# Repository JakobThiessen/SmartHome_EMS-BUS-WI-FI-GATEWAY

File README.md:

# SmartHome_EMS-BUS-WI-FI-GATEWAY
ESP32-EMS WiFi gateway for read and control EMS and Heatronic compatible devices such as boilers, thermostats, solar modules and heat pumps.

# Software Project

https://github.com/emsesp/EMS-ESP32

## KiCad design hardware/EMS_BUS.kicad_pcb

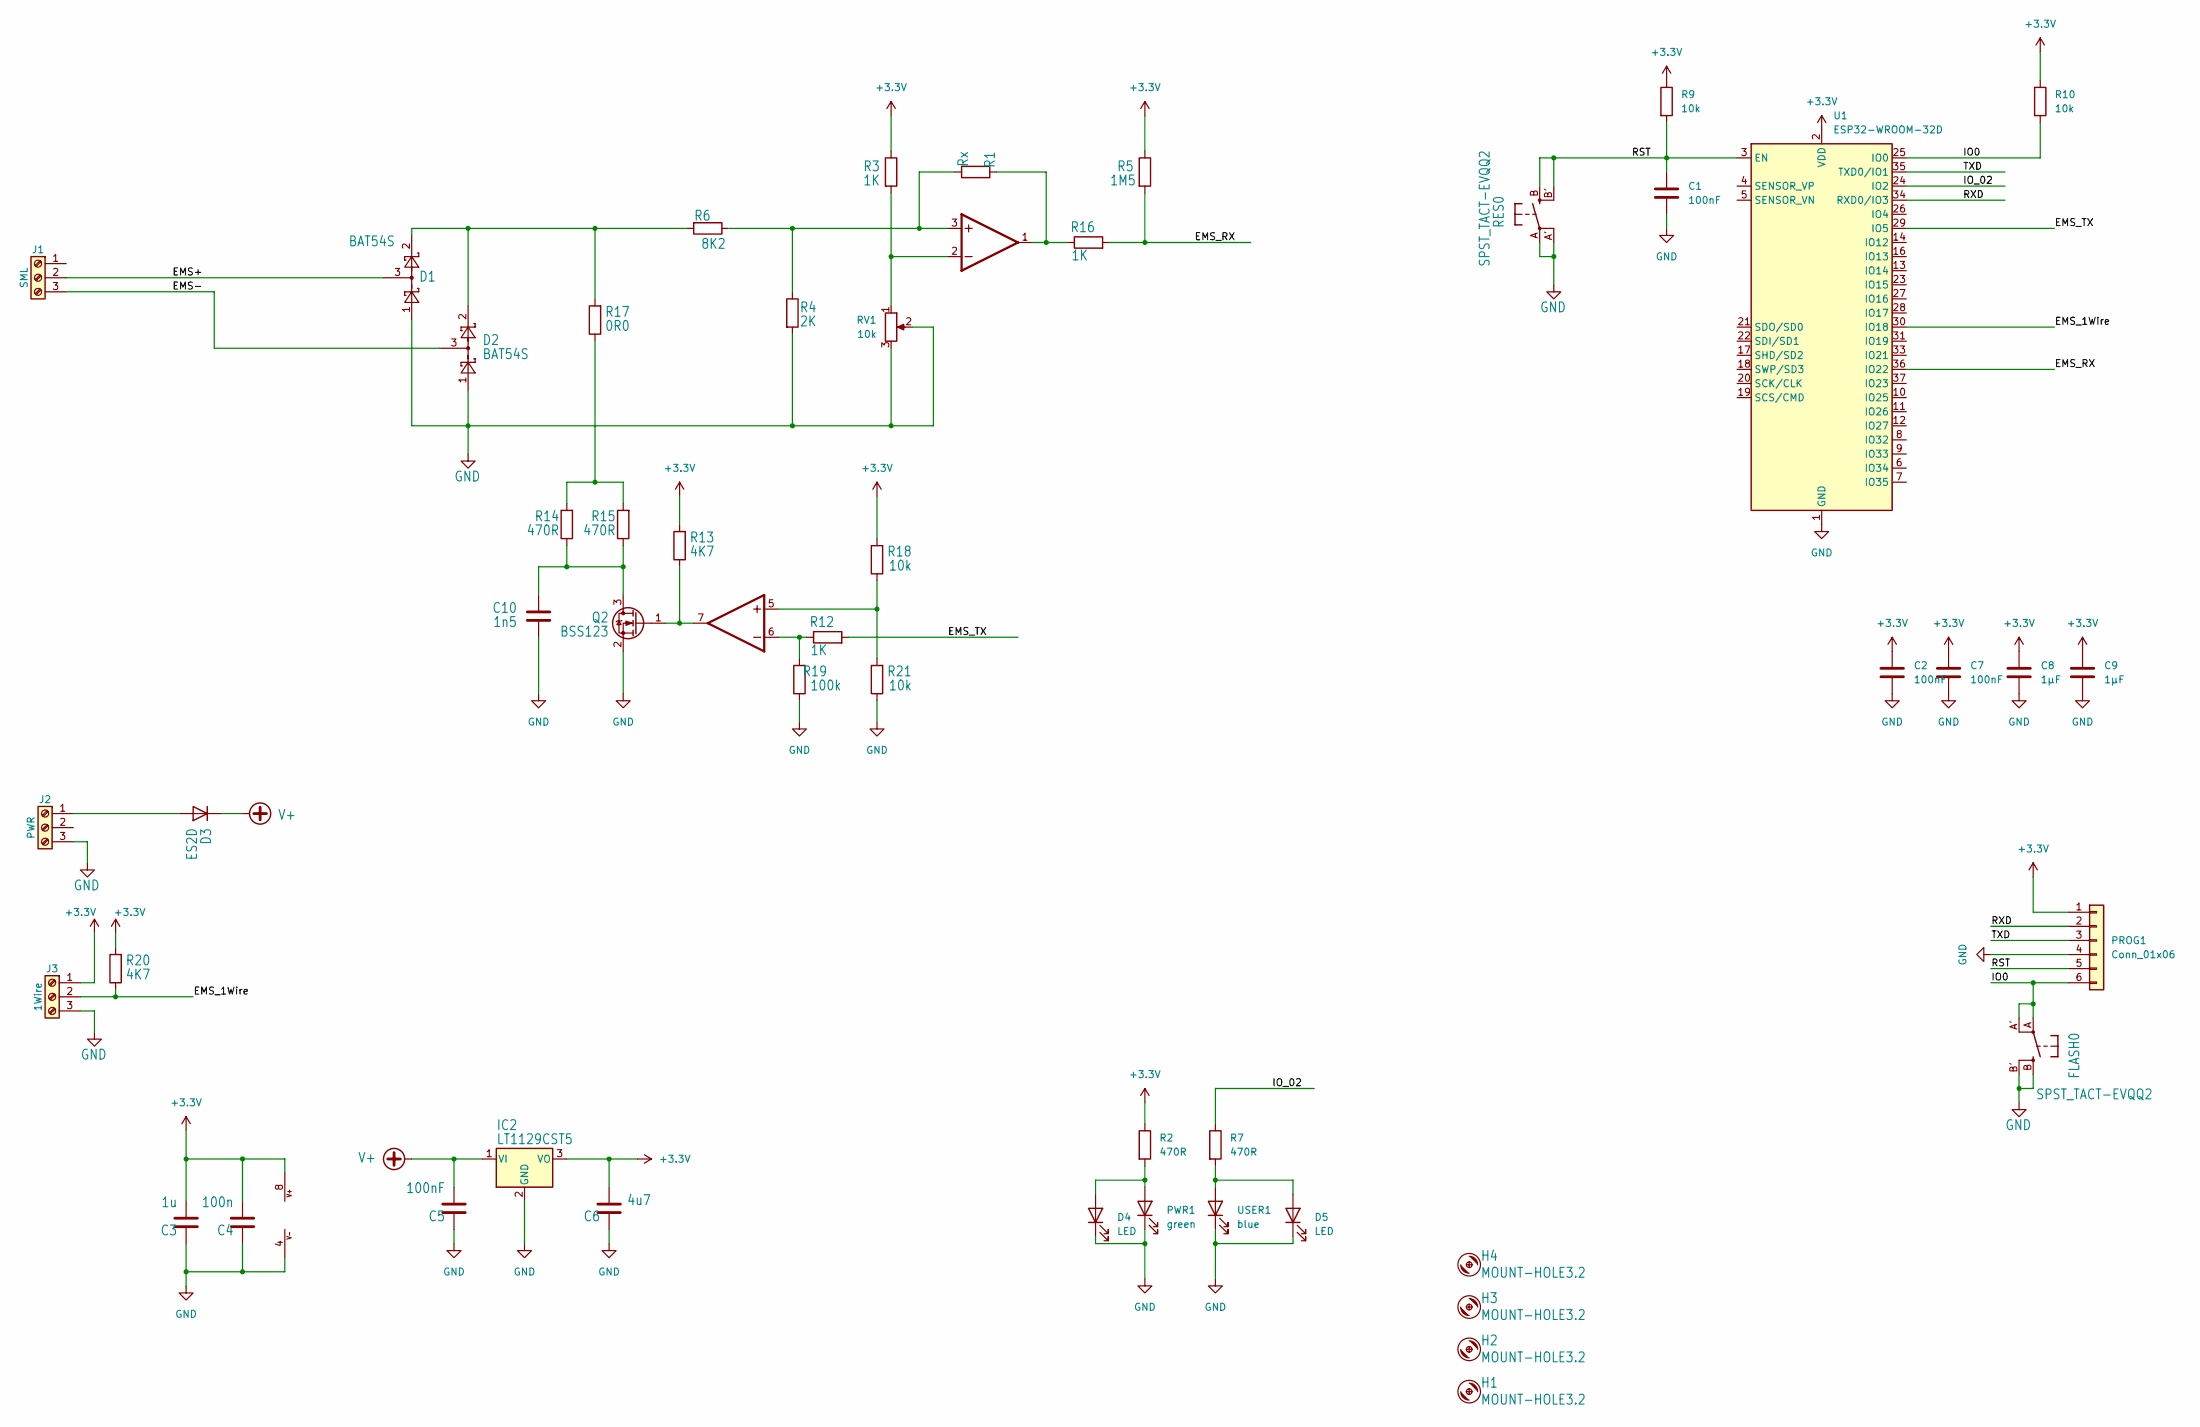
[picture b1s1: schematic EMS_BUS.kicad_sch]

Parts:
C1, C2, C5, C7: 100nF; C_0603_1608Metric
C3: 1u; C_0603_1608Metric
C4: 100n; C_0603_1608Metric
C6: 4u7; C_0603_1608Metric
C8, C9: 1µF; C_0603_1608Metric
C10: 1n5; C_0603_1608Metric
D1, D2: BAT54S; SOT-23
D3: ES2D; D_SMB
D4, D5: LED; LED_D3.0mm_Clear
FLASH0: SPST_TACT-EVQQ2; EVQ-Q2
H1, H2, H3, H4: MOUNT-HOLE3.2; 3,2
IC1: LM393D; SO08
IC2: LT1129CST5; SOT-223-3_TabPin2
J1: SML; PhoenixContact_MC_1,5_3-G-3.5_1x03_P3.50mm_Horizontal
J2: PWR; PhoenixContact_MC_1,5_3-G-3.81_1x03_P3.81mm_Horizontal
J3: 1Wire; JST_XA_B03B-XASK-1-A_1x03_P2.50mm_Vertical
PROG1: Conn_01x06; PinHeader_1x06_P2.54mm_Vertical
PWR1: green; LED_0603_1608Metric
Q2: BSS123; SOT-23
R1: Rx; R_0603_1608Metric
R2, R7, R14, R15: 470R; R_0603_1608Metric
R3, R12, R16: 1K; R_0603_1608Metric
R4: 2K; R_0603_1608Metric
R5: 1M5; R_0603_1608Metric
R6: 8K2; R_0603_1608Metric
R9, R10, R18, R21: 10k; R_0603_1608Metric
R13, R20: 4K7; R_0603_1608Metric
R17: 0R0; R_0603_1608Metric
R19: 100k; R_0603_1608Metric
RES0: SPST_TACT-EVQQ2; EVQ-Q2
RV1: 10k; Potentiometer_Bourns_3296Y_Vertical
U1: ESP32-WROOM-32D; ESP32-WROOM-32
USER1: blue; LED_0603_1608Metric

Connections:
+3.3V: C2.1, C3.2, C4.2, C6.2, C7.1, C8.1, C9.1, IC1.8 (V+), IC2.3 (VO), J3.1, PROG1.1, R2.1, R3.1, R5.1, R9.1, R10.1, R13.2, R18.2, R20.2, U1.2 (VDD)
+VDC: C5.2, D3.1 (K), IC2.1 (VI)
/EMS+: D1.3, J1.2
/EMS-: D2.3, J1.3
/EMS_1Wire: J3.2, R20.1, U1.30 (IO18)
/EMS_RX: R5.2, R16.2, U1.36 (IO22)
/EMS_TX: R12.2, U1.29 (IO5)
/IO0: FLASH0.A, FLASH0.A' (P1), PROG1.6, R10.2, U1.25 (IO0)
/IO_02: R7.1, U1.24 (IO2)
/RST: C1.1, PROG1.5, R9.2, RES0.B (S), RES0.B' (S1), U1.3 (EN)
/RXD: PROG1.2, U1.34 (RXD0/IO3)
/TXD: PROG1.3, U1.35 (TXD0/IO1)
GND: C1.2, C2.2, C3.1, C4.1, C5.1, C6.1, C7.2, C8.2, C9.2, C10.1, D1.1, D2.1, D4.1 (K), D5.1 (K), FLASH0.B (S), FLASH0.B' (S1), IC1.4 (V-), IC2.2 (GND), J2.3, J3.3, PROG1.4, PWR1.1 (K), Q2.2 (S), R4.2, R19.1, R21.1, RES0.A, RES0.A' (P1), RV1.2, RV1.3, U1.1 (GND), U1.15 (GND), U1.38 (GND), U1.39 (GND), USER1.1 (K)
unnamed: C10.2, Q2.3 (D), R14.1, R15.1
unnamed: D1.2, D2.2, R6.2, R17.2
unnamed: D3.2 (A), J2.1
unnamed: IC1.1 (OUT), R1.1, R16.1
unnamed: IC1.2 (-IN), R3.2, RV1.1
unnamed: IC1.3 (+IN), R1.2, R4.1, R6.1
unnamed: IC1.5 (+IN), R18.1, R21.2
unnamed: IC1.6 (-IN), R12.1, R19.2
unnamed: IC1.7 (OUT), Q2.1 (G), R13.1
unnamed: D4.2 (A), PWR1.2 (A), R2.2
unnamed: D5.2 (A), R7.2, USER1.2 (A)
unnamed: R14.2, R15.2, R17.1

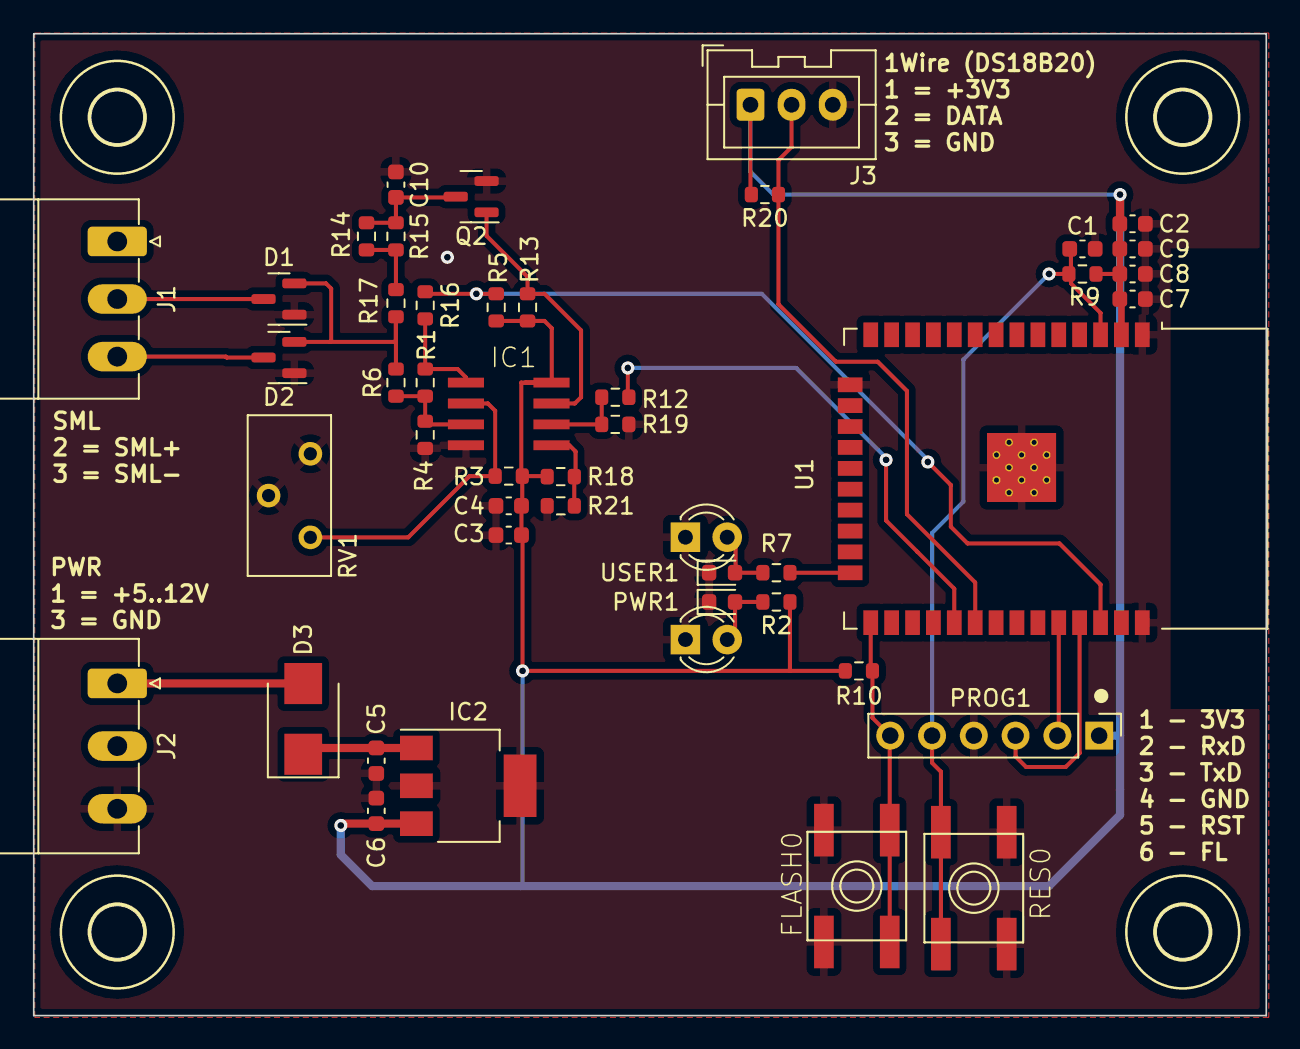
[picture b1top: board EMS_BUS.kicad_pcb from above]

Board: 2 copper layers, 74.9 x 59.7 mm, 51 parts (0 on the bottom side), 25 nets.

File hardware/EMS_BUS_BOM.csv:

Item;Qty;Reference(s);Value;Footprint
;;C1;100nF;0603
;;C2;100nF;0603
;;C3;1u;0603
;;C4;100n;0603
;;C5;100nF;0603
;;C6;4u7;0603
;;C7;100nF;0603
;;C8;1µF;0603
;;C9;1µF;0603
;;C10;1n5;0603
;;D1;BAT54S;SOT-23
;;D2;BAT54S;SOT-23
;;D3;ES2D;D_SMB
;;D4;LED;LED_D3.0mm_Clear
;;D5;LED;LED_D3.0mm_Clear
;;FLASH0;SPST_TACT-EVQQ2;EVQ-Q2
;;H1;MOUNT-HOLE3.2;
;;H2;MOUNT-HOLE3.2;
;;H3;MOUNT-HOLE3.2;
;;H4;MOUNT-HOLE3.2;
;;IC1;LM393D;SO08
;;IC2;LT1129CST5;SOT-223-3
;;J1;SML;PhoenixContact_MC_1,5_3-G-3.5
;;J2;PWR;PhoenixContact_MC_1,5_3-G-3.81
;;J3;1Wire;JST_XA_B03B-XASK-1-A_1x03_P2.50mm_Vertical
;;PROG1;Conn_01x06;Connector_PinHeader_2.54mm
;;PWR1;green;0603
;;Q2;BSS123;SOT-23
;;R1;Rx;0603
;;R2;470R;0603
;;R3;1K;0603
;;R4;2K;0603
;;R5;1M5;0603
;;R6;8K2;0603
;;R7;470R;0603
;;R9;10k;0603
;;R10;10k;0603
;;R12;1K;0603
;;R13;4K7;0603
;;R14;470R;0603
;;R15;470R;0603
;;R16;1K;0603
;;R17;0R0;0603
;;R18;10k;0603
;;R19;100k;0603
;;R20;4K7;0603
;;R21;10k;0603
;;RES0;SPST_TACT-EVQQ2;EVQ-Q2
;;RV1;10k;Bourns_3296Y_Vertical
;;U1;ESP32-WROOM-32D;ESP32-WROOM-32
;;USER1;blue;LED_SMD_0603
;;;;
;;;;
;;;;
Collated Components:;;;;
;;;;
Item;Qty;Reference(s);Value;Footprint
1;4;C1, C2, C5, C7;100nF;Capacitor_SMD
2;1;C3;1u;Capacitor_SMD
3;1;C4;100n;Capacitor_SMD
4;1;C6;4u7;Capacitor_SMD
5;2;C8, C9;1ÂµF;Capacitor_SMD
6;1;C10;1n5;Capacitor_SMD
7;2;D1, D2;BAT54S;Package_TO_SOT_SMD
8;1;D3;ES2D;Diode_SMD
9;2;D4, D5;LED;LED_THT
10;2;FLASH0, RES0;SPST_TACT-EVQQ2;main
11;4;H1, H2, H3, H4;MOUNT-HOLE3.2;main
12;1;IC1;LM393D;main
13;1;IC2;LT1129CST5;Package_TO_SOT_SMD
14;1;J1;SML;Connector_Phoenix_MC
15;1;J2;PWR;Connector_Phoenix_MC
16;1;J3;1Wire;Connector_JST
17;1;PROG1;Conn_01x06;Connector_PinHeader_2.54mm
18;1;PWR1;green;LED_SMD
19;1;Q2;BSS123;Package_TO_SOT_SMD
20;1;R1;Rx;Resistor_SMD
21;4;R2, R7, R14, R15;470R;Resistor_SMD
22;3;R3, R12, R16;1K;Resistor_SMD
23;1;R4;2K;Resistor_SMD
24;1;R5;1M5;Resistor_SMD
25;1;R6;8K2;Resistor_SMD
26;4;R9, R10, R18, R21;10k;Resistor_SMD
27;2;R13, R20;4K7;Resistor_SMD
28;1;R17;0R0;Resistor_SMD
29;1;R19;100k;Resistor_SMD
30;1;RV1;10k;Potentiometer_THT
31;1;U1;ESP32-WROOM-32D;RF_Module
32;1;USER1;blue;LED_SMD

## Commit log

2023-01-21 Dokumentation erstellt
2023-01-21 3D Bild hinzugefügt
2023-02-11 kleine Änderungen add gerber.zip
2023-02-11 add BOM
